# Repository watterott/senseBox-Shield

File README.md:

# senseBox-Shield
The senseBox-Shield is a plug-on module for Arduino to connect different sensor modules.

* JST connectors for different sensors
* microSD socket (SPI) support SD and SDHC cards
* RV-8523 RTC (I2C Real-Time-Clock) with backup battery
* Open-Source
* **[Documentation on learn.watterott.com](https://learn.watterott.com)**

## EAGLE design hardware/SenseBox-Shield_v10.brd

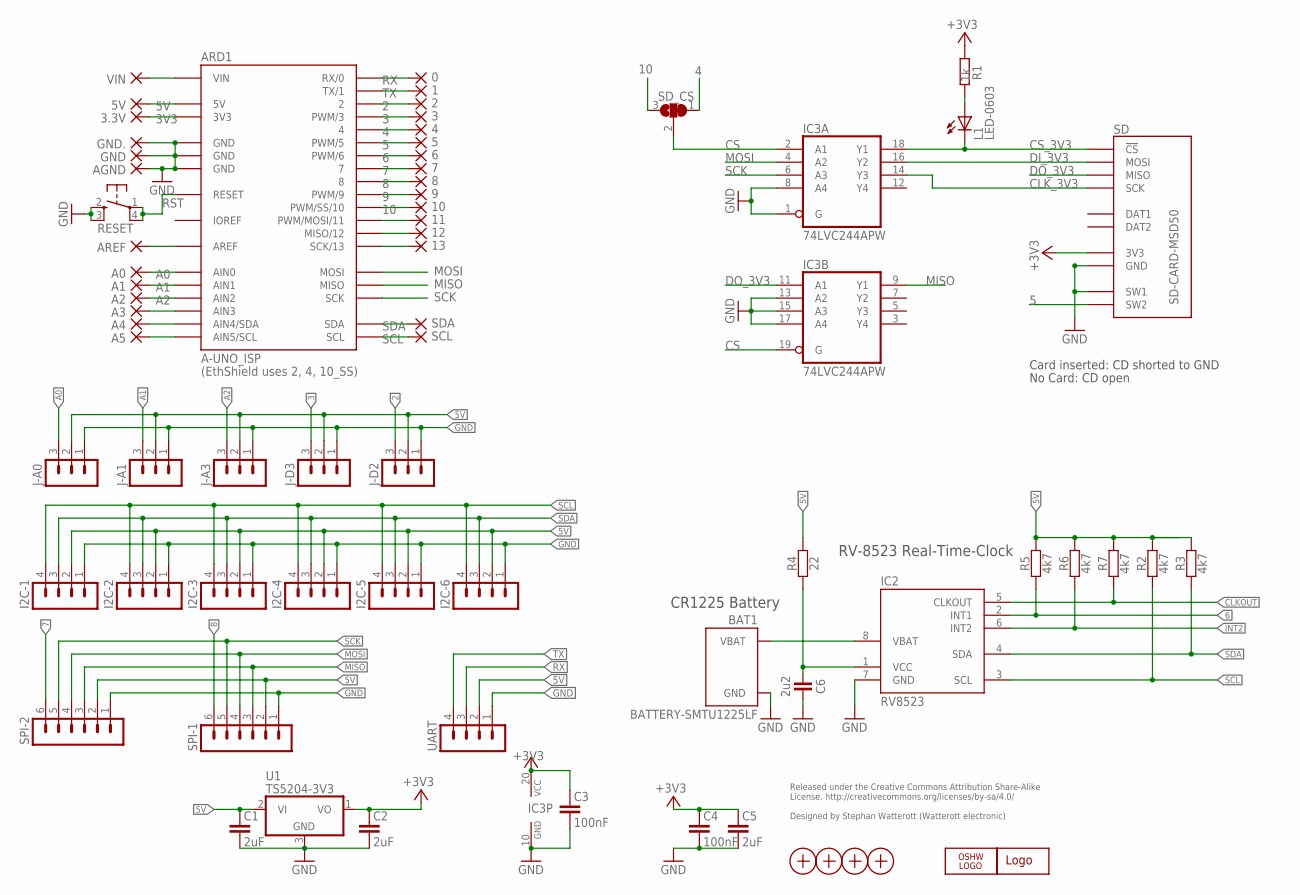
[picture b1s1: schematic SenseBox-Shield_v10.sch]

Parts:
0, 1, 2, 3, 3.3V, 4, 5, 5V, 6, 7, 8, 9, 10, 11, 12, 13: 1,6/0,8
A0, A1, A2, A3, A4, A5: 1,6/0,8
AGND: 1,6/0,8
ARD1: A-UNO_ISP; A-UNO-ISP
AREF: 1,6/0,8
BAT1: BATTERY-SMTU1225LF; BAT-SMTU1225LF
C1, C2: 2uF; C0805
C3, C4: 100nF; C0603
C5: 2uF; C0603
C6: 2u2; R0603
GND, GND.: 1,6/0,8
I2C-1, I2C-2, I2C-3, I2C-4, I2C-5, I2C-6: JST_PH_4B4B-PH-SM4-TB; JST_B4B-PH-SM4-TB
IC2: RV8523; RTC-C3
IC3: 74LVC244APW; TSSOP20
J-A0, J-A1, J-A3: JST_PH_3B3B-PH-SM4-TB; JST_B3B-PH-SM4-TB
J-D2, J-D3: JST_PH_3B3B-PH-SM4-TB; JST_B3B-PH-SM4-TB
L1: LED-0603; LED_0603
LOGO2: WE-LOGOPLACE; WE-LOGO
LOGO3: OSHW_LOGO_6MILX0100-NT; OSHW_6X100_NOTEXT
R1: 1k; R0603
R2, R3, R5, R6, R7: 4k7; R0603
R4: 22; R0603
RESET: SW4S; SW_SMD4
SCL: 1,6/0,8
SD: SD-CARD-MSD50; SD_5031821853
SDA: 1,6/0,8
SD_CS: SJ2W; SJ_2
SPI-1, SPI-2: JST_PH_6B6B-PH-SM4-TB; JST_B6B-PH-SM4-TB
U1: TS5204-3V3; SOT23
UART: JST_PH_4B4B-PH-SM4-TB; JST_B4B-PH-SM4-TB
VIN: 1,6/0,8
X1, X2, X3, X4: PASSER

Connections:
2: 2.1, ARD1.2, J-D2.3
3: 3.1, ARD1.3 (PWM/3), J-D3.3
3V3: 3.3V.1, ARD1.3V3
4: 4.1, ARD1.4, SD_CS.1
5: 5.1, ARD1.5 (PWM/5), SD.SW2
5V: 5V.1, ARD1.5V, C1.1, I2C-1.2, I2C-2.2, I2C-3.2, I2C-4.2, I2C-5.2, I2C-6.2, J-A0.2, J-A1.2, J-A3.2, J-D2.2, J-D3.2, R2.2, R3.2, R4.2, R5.2, R6.2, R7.2, SPI-1.2, SPI-2.2, U1.2 (VI), UART.2
6: 6.1, ARD1.6 (PWM/6), IC2.2 (INT1), R5.1
7: 7.1, ARD1.7, SPI-2.6
8: 8.1, ARD1.8, SPI-1.6
9: 9.1, ARD1.9 (PWM/9)
10: 10.1, ARD1.10 (PWM/SS/10), SD_CS.3
11: 11.1, ARD1.11 (PWM/MOSI/11)
12: 12.1, ARD1.12 (MISO/12)
13: 13.1, ARD1.13 (SCK/13)
+3V3: C2.1, C3.1, C4.1, C5.1, IC3.20 (VCC), R1.1, SD.VCC (3V3), U1.1 (VO)
A0: A0.1, ARD1.A0 (AIN0), J-A0.3
A1: A1.1, ARD1.A1 (AIN1), J-A1.3
A2: A2.1, ARD1.A2 (AIN2), J-A3.3
AIN3: A3.1, ARD1.A3 (AIN3)
AIN4: A4.1, ARD1.A4 (AIN4/SDA)
AIN5: A5.1, ARD1.A5 (AIN5/SCL)
AREF: ARD1.AREF, AREF.1
CLKOUT: IC2.5 (CLKOUT), R7.1
CLK_3V3: IC3.14 (Y3), SD.SCK
CS: IC3.2 (A1), IC3.19 (G), SD_CS.2
CS_3V3: IC3.18 (Y1), L1.C, SD.CS (!CS)
DI_3V3: IC3.16 (Y2), SD.MOSI
DO_3V3: IC3.11 (A1), SD.MISO
GND: AGND.1, ARD1.GND@1 (GND), ARD1.GND@2 (GND), ARD1.GND@3 (GND), BAT1.- (GND), C1.2, C2.2, C3.2, C4.2, C5.2, C6.2, GND.1, GND..1, I2C-1.1, I2C-2.1, I2C-3.1, I2C-4.1, I2C-5.1, I2C-6.1, IC2.7 (GND), IC3.1 (G), IC3.8 (A4), IC3.10 (GND), IC3.13 (A2), IC3.15 (A3), IC3.17 (A4), J-A0.1, J-A1.1, J-A3.1, J-D2.1, J-D3.1, RESET.2 (S), RESET.3 (S1), SD.GND, SD.SW1, SPI-1.1, SPI-2.1, U1.3 (GND), UART.1
INT2: IC2.6 (INT2), R6.1
IOREF: ARD1.IOREF
MISO: ARD1.MISO, IC3.9 (Y1), SPI-1.3, SPI-2.3
MOSI: ARD1.MOSI, IC3.4 (A2), SPI-1.4, SPI-2.4
unnamed: L1.A, R1.2
RST: ARD1.RST (RESET), RESET.1, RESET.4 (P1)
RV_VCC: C6.1, IC2.1 (VCC), R4.1
RX: 0.1, ARD1.0 (RX/0), UART.3
SCK: ARD1.SCK, IC3.6 (A3), SPI-1.5, SPI-2.5
SCL: ARD1.SCL, I2C-1.4, I2C-2.4, I2C-3.4, I2C-4.4, I2C-5.4, I2C-6.4, IC2.3 (SCL), R2.1, SCL.1
SDA: ARD1.SDA, I2C-1.3, I2C-2.3, I2C-3.3, I2C-4.3, I2C-5.3, I2C-6.3, IC2.4 (SDA), R3.1, SDA.1
TX: 1.1, ARD1.1 (TX/1), UART.4
VBAT: BAT1.+ (VBAT), IC2.8 (VBAT)
VIN: ARD1.VIN, VIN.1

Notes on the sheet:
Released under the Creative Commons Attribution Share-Alike License. http://creativecommons.org/licenses/by-sa/4.0/ Designed by Stephan Watterott (Watterott electronic)
(EthShield uses 2, 4, 10_SS)
Card inserted: CD shorted to GND
No Card: CD open
RV-8523 Real-Time-Clock
CR1225 Battery

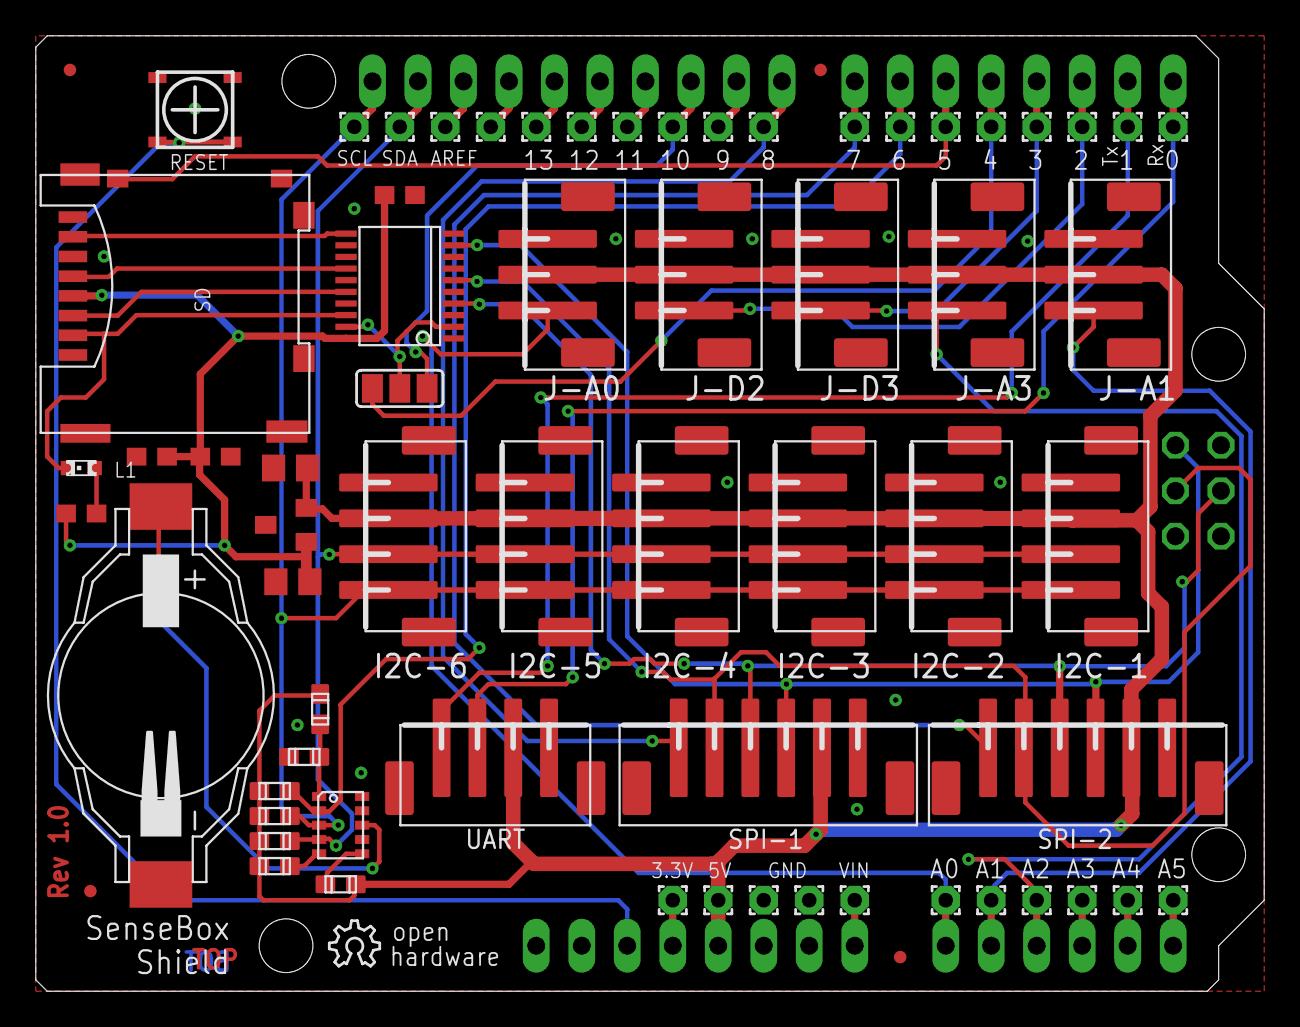
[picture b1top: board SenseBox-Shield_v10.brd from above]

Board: 2 copper layers, 68.6 x 53.3 mm, 71 parts (1 on the bottom side), 42 nets.

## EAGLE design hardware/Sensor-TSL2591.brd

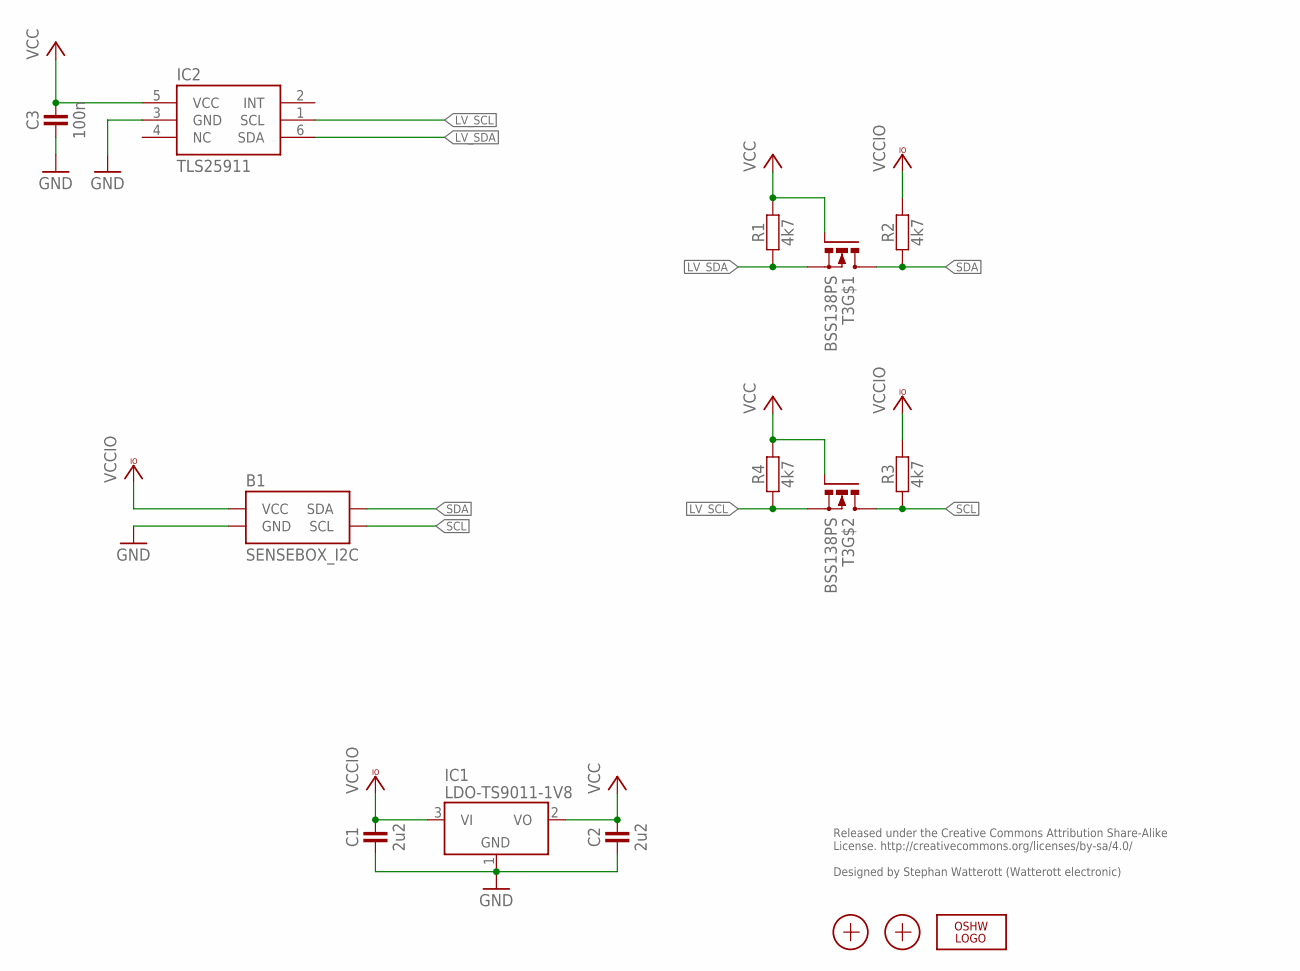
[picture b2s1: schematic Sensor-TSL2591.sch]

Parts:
B1: SENSEBOX_I2C; BREAKOUT_SENSEBOX_I2C
C1, C2: 2u2; R0402
C3: 100n; R0402
IC1: LDO-TS9011-1V8; SOT23
IC2: TLS25911; WFDFN6
LOGO2: OSHW_LOGOX0070; OSHW_6X70
R1, R2, R3, R4: 4k7; R0402
T3: BSS138PS; SOT363
X1, X2: PASSER-07; PASSER_07MM

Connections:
GND: B1.GND, C1.1, C2.1, C3.1, IC1.1 (GND), IC2.3 (GND)
LV_SCL: IC2.1 (SCL), R4.1, T3.4 (S)
LV_SDA: IC2.6 (SDA), R1.1, T3.1 (S)
SCL: B1.SCL, R3.1, T3.3 (D)
SDA: B1.SDA, R2.1, T3.6 (D)
VCC: C2.2, C3.2, IC1.2 (VO), IC2.5 (VCC), R1.2, R4.2, T3.2 (G), T3.5 (G)
VCCIO: B1.VCC, C1.2, IC1.3 (VI), R2.2, R3.2

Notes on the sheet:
Released under the Creative Commons Attribution Share-Alike License. http://creativecommons.org/licenses/by-sa/4.0/ Designed by Stephan Watterott (Watterott electronic)

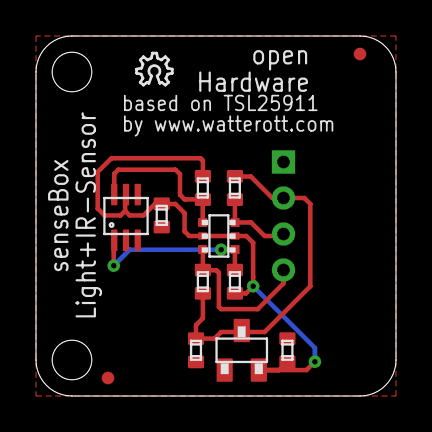
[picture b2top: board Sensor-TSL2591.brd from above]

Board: 2 copper layers, 20.0 x 20.0 mm, 14 parts (0 on the bottom side), 7 nets.

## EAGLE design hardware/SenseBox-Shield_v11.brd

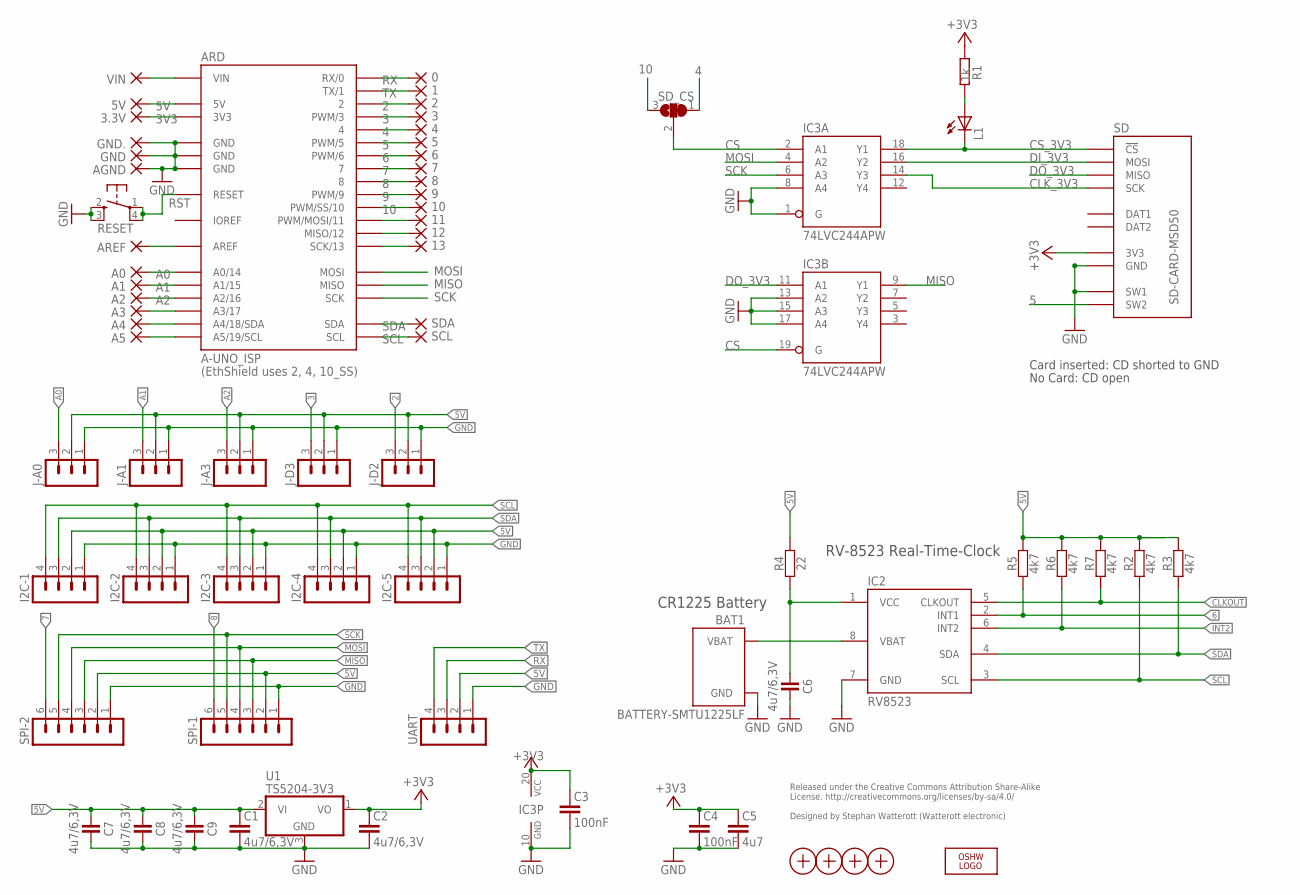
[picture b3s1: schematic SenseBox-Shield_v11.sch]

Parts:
0, 1, 2, 3, 3.3V, 4, 5, 5V, 6, 7, 8, 9, 10, 11, 12, 13: 1,6/0,8
A0, A1, A2, A3, A4, A5: 1,6/0,8
AGND: 1,6/0,8
ARD: A-UNO_ISP; A-UNO-ISP
AREF: 1,6/0,8
BAT1: BATTERY-SMTU1225LF; BAT-SMTU1225LF
C1, C2: 4u7/6,3V; C0402K
C3, C4: 100nF; C0402K
C5: 4u7; C0402K
C6, C7, C8, C9: 4u7/6,3V; C0402
GND, GND.: 1,6/0,8
I2C-1, I2C-2, I2C-3, I2C-4, I2C-5: JST_PH_4B4B-PH-SM4-TB; JST_B4B-PH-SM4-TB
IC2: RV8523; RTC-C3
IC3: 74LVC244APW; TSSOP20
J-A0, J-A1, J-A3: JST_PH_3B3B-PH-SM4-TB; JST_B3B-PH-SM4-TB
J-D2, J-D3: JST_PH_3B3B-PH-SM4-TB; JST_B3B-PH-SM4-TB
L1: LED-0603; C0603
LOGO3: OSHW_LOGO_6MILX0100-NT; OSHW_6X100_NOTEXT
R1: 1k; R0402
R2, R3, R5, R6, R7: 4k7; C0402
R4: 22; C0402
RESET: SW4S; SW_SMD4
SCL: 1,6/0,8
SD: SD-CARD-MSD50; SD_5031821853
SDA: 1,6/0,8
SD_CS: SJ2W; SJ_2
SPI-1, SPI-2: JST_PH_6B6B-PH-SM4-TB; JST_B6B-PH-SM4-TB
U1: TS5204-3V3; SOT23
UART: JST_PH_4B4B-PH-SM4-TB; JST_B4B-PH-SM4-TB
VIN: 1,6/0,8
X1, X2, X3, X4: PASSER

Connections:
2: 2.1, ARD.2, J-D2.3
3: 3.1, ARD.3 (PWM/3), J-D3.3
3V3: 3.3V.1, ARD.3V3
4: 4.1, ARD.4, SD_CS.1
5: 5.1, ARD.5 (PWM/5), SD.SW2
5V: 5V.1, ARD.5V, C1.1, C7.1, C8.1, C9.1, I2C-1.2, I2C-2.2, I2C-3.2, I2C-4.2, I2C-5.2, J-A0.2, J-A1.2, J-A3.2, J-D2.2, J-D3.2, R2.2, R3.2, R4.2, R5.2, R6.2, R7.2, SPI-1.2, SPI-2.2, U1.2 (VI), UART.2
6: 6.1, ARD.6 (PWM/6), IC2.2 (INT1), R5.1
7: 7.1, ARD.7, SPI-2.6
8: 8.1, ARD.8, SPI-1.6
9: 9.1, ARD.9 (PWM/9)
10: 10.1, ARD.10 (PWM/SS/10), SD_CS.3
11: 11.1, ARD.11 (PWM/MOSI/11)
12: 12.1, ARD.12 (MISO/12)
13: 13.1, ARD.13 (SCK/13)
+3V3: C2.1, C3.1, C4.1, C5.1, IC3.20 (VCC), R1.1, SD.VCC (3V3), U1.1 (VO)
A0: A0.1, ARD.A0 (A0/14), J-A0.3
A1: A1.1, ARD.A1 (A1/15), J-A1.3
A2: A2.1, ARD.A2 (A2/16), J-A3.3
AIN3: A3.1, ARD.A3 (A3/17)
AIN4: A4.1, ARD.A4 (A4/18/SDA)
AIN5: A5.1, ARD.A5 (A5/19/SCL)
AREF: ARD.AREF, AREF.1
CLKOUT: IC2.5 (CLKOUT), R7.1
CLK_3V3: IC3.14 (Y3), SD.SCK
CS: IC3.2 (A1), IC3.19 (G), SD_CS.2
CS_3V3: IC3.18 (Y1), L1.C, SD.CS (!CS)
DI_3V3: IC3.16 (Y2), SD.MOSI
DO_3V3: IC3.11 (A1), SD.MISO
GND: AGND.1, ARD.GND@1 (GND), ARD.GND@2 (GND), ARD.GND@3 (GND), BAT1.- (GND), C1.2, C2.2, C3.2, C4.2, C5.2, C6.2, C7.2, C8.2, C9.2, GND.1, GND..1, I2C-1.1, I2C-2.1, I2C-3.1, I2C-4.1, I2C-5.1, IC2.7 (GND), IC3.1 (G), IC3.8 (A4), IC3.10 (GND), IC3.13 (A2), IC3.15 (A3), IC3.17 (A4), J-A0.1, J-A1.1, J-A3.1, J-D2.1, J-D3.1, RESET.2 (S), RESET.3 (S1), SD.GND, SD.SW1, SPI-1.1, SPI-2.1, U1.3 (GND), UART.1
INT2: IC2.6 (INT2), R6.1
IOREF: ARD.IOREF
MISO: ARD.MISO, IC3.9 (Y1), SPI-1.3, SPI-2.3
MOSI: ARD.MOSI, IC3.4 (A2), SPI-1.4, SPI-2.4
unnamed: L1.A, R1.2
RST: ARD.RST@1 (RESET), RESET.1, RESET.4 (P1)
RV_VCC: C6.1, IC2.1 (VCC), R4.1
RX: 0.1, ARD.0 (RX/0), UART.3
SCK: ARD.SCK, IC3.6 (A3), SPI-1.5, SPI-2.5
SCL: ARD.SCL, I2C-1.4, I2C-2.4, I2C-3.4, I2C-4.4, I2C-5.4, IC2.3 (SCL), R2.1, SCL.1
SDA: ARD.SDA, I2C-1.3, I2C-2.3, I2C-3.3, I2C-4.3, I2C-5.3, IC2.4 (SDA), R3.1, SDA.1
TX: 1.1, ARD.1 (TX/1), UART.4
VBAT: BAT1.+ (VBAT), IC2.8 (VBAT)
VIN: ARD.VIN, VIN.1

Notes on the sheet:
Released under the Creative Commons Attribution Share-Alike License. http://creativecommons.org/licenses/by-sa/4.0/ Designed by Stephan Watterott (Watterott electronic)
(EthShield uses 2, 4, 10_SS)
Card inserted: CD shorted to GND
No Card: CD open
RV-8523 Real-Time-Clock
CR1225 Battery

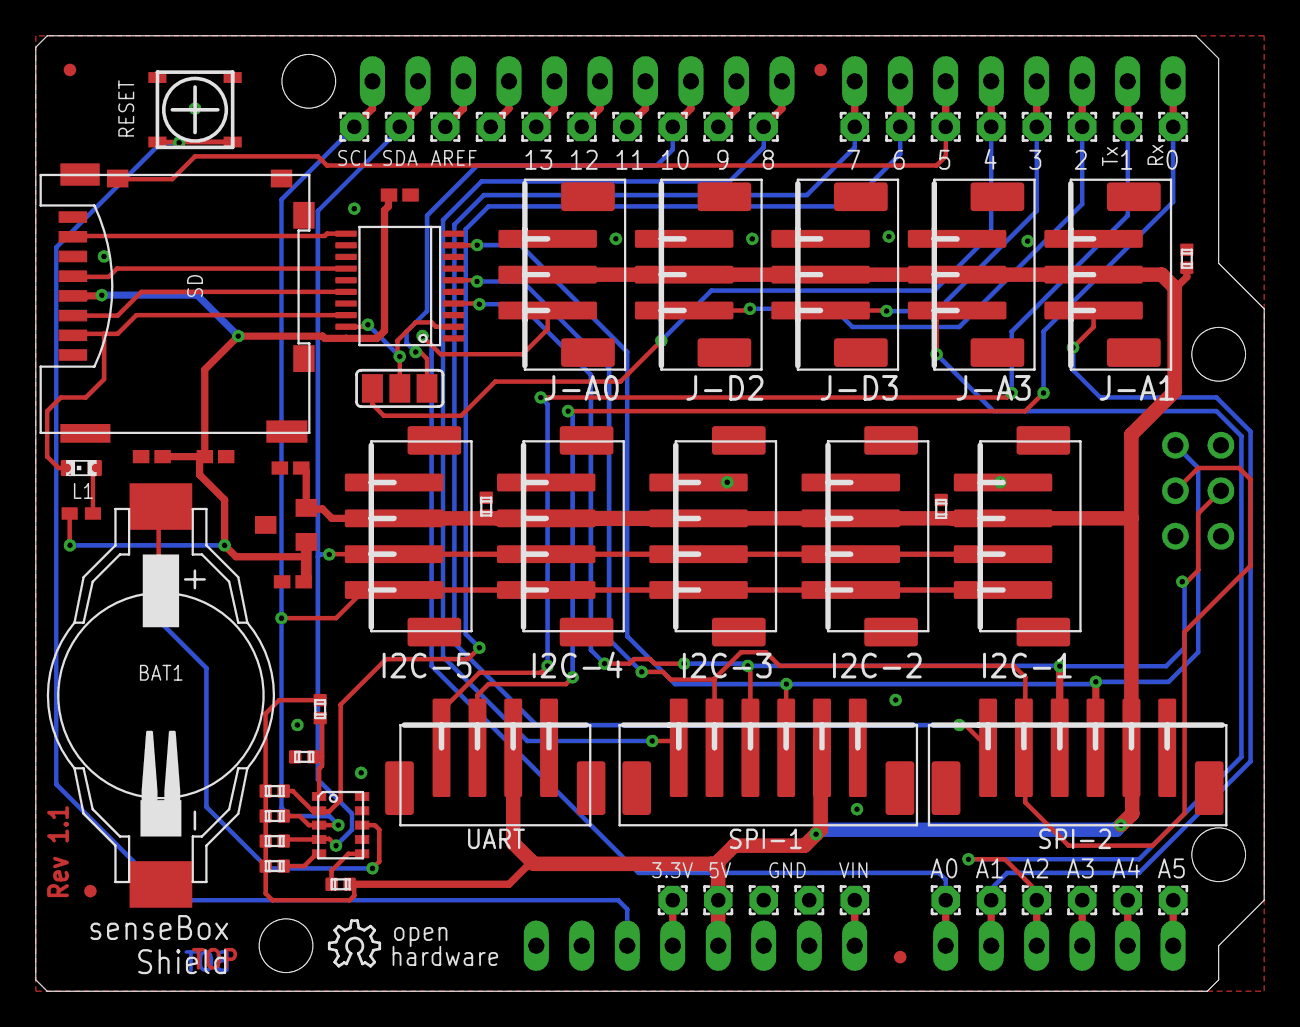
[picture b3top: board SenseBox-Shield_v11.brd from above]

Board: 2 copper layers, 68.6 x 53.3 mm, 72 parts (0 on the bottom side), 42 nets.

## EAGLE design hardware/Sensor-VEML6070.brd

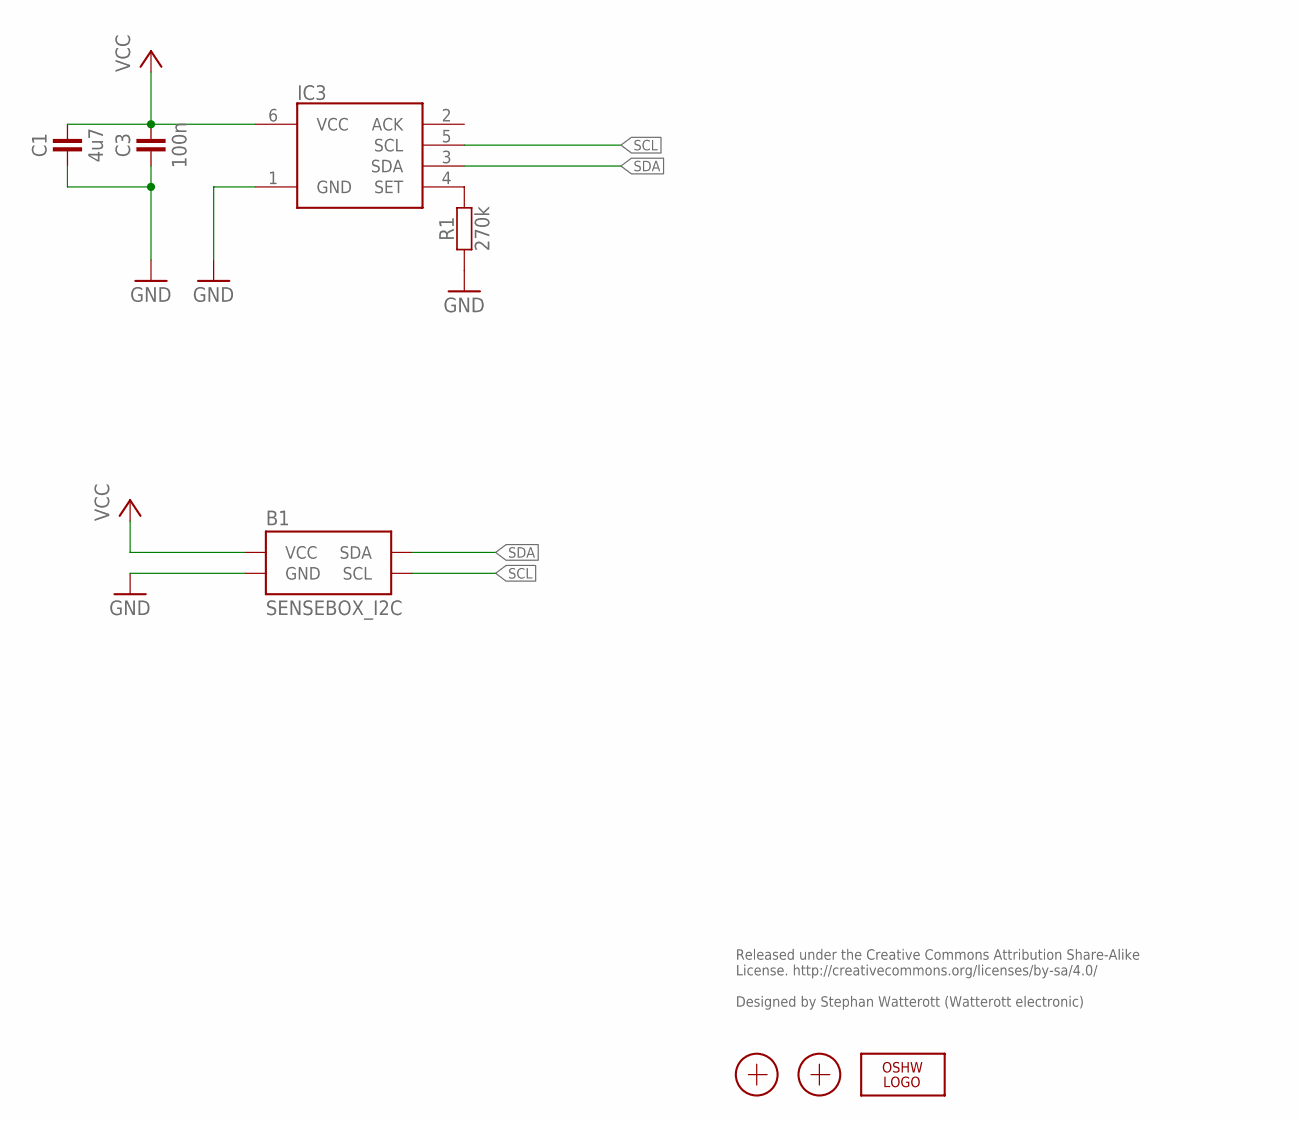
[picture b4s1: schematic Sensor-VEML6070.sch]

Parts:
B1: SENSEBOX_I2C; BREAKOUT_SENSEBOX_I2C
C1: 4u7; R0402
C3: 100n; R0402
IC3: VEML6070; OPLGA
LOGO2: OSHW_LOGOX0070; OSHW_6X70
R1: 270k; R0402
X1, X2: PASSER-07; PASSER_07MM

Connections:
GND: B1.GND, C1.1, C3.1, IC3.1 (GND), R1.1
unnamed: IC3.4 (SET), R1.2
SCL: B1.SCL, IC3.5 (SCL)
SDA: B1.SDA, IC3.3 (SDA)
VCC: B1.VCC, C1.2, C3.2, IC3.6 (VCC)

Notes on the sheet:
Released under the Creative Commons Attribution Share-Alike License. http://creativecommons.org/licenses/by-sa/4.0/ Designed by Stephan Watterott (Watterott electronic)

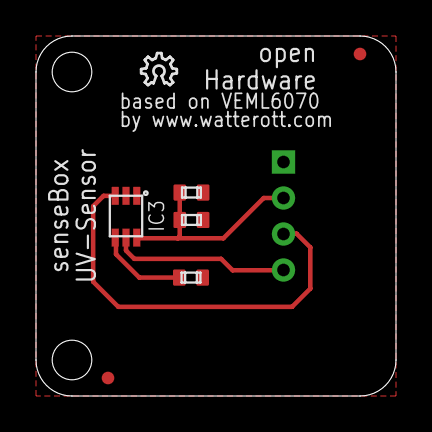
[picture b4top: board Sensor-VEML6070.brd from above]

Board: 2 copper layers, 20.0 x 20.0 mm, 8 parts (0 on the bottom side), 5 nets.

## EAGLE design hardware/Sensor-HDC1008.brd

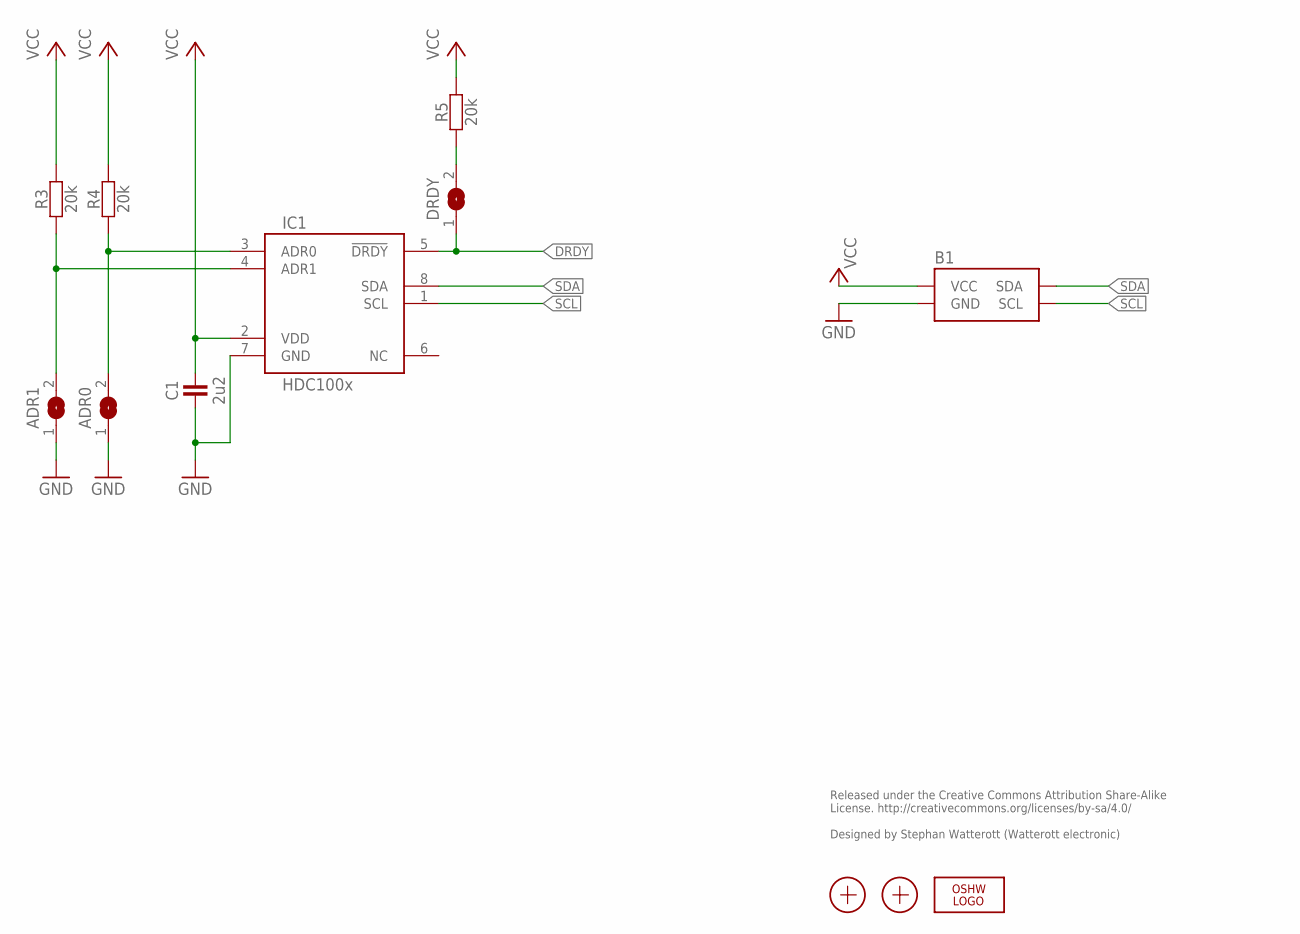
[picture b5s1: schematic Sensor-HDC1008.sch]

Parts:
ADR0, ADR1: JUMPER2-0402
B1: SENSEBOX_I2C
C1: 2u2; R0402
DRDY: JUMPER2-0402
IC1: HDC100x; WLCSP
LOGO2: OSHW_LOGOX0070; OSHW_6X70
R3, R4, R5: 20k; R0402
X1, X2: PASSER-07; PASSER_07MM

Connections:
ADR0: ADR0.2, IC1.3 (ADR0), R4.1
ADR1: ADR1.2, IC1.4 (ADR1), R3.1
DRDY: DRDY.1, IC1.5 (!DRDY)
GND: ADR0.1, ADR1.1, B1.GND, C1.1, IC1.7 (GND)
unnamed: DRDY.2, R5.1
SCL: B1.SCL, IC1.1 (SCL)
SDA: B1.SDA, IC1.8 (SDA)
VCC: B1.VCC, C1.2, IC1.2 (VDD), R3.2, R4.2, R5.2

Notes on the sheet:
Released under the Creative Commons Attribution Share-Alike License. http://creativecommons.org/licenses/by-sa/4.0/ Designed by Stephan Watterott (Watterott electronic)

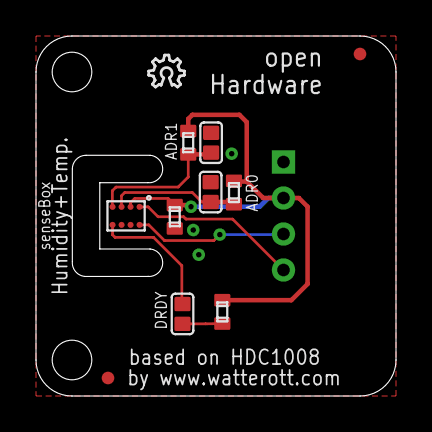
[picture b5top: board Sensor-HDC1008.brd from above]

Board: 2 copper layers, 20.0 x 20.0 mm, 12 parts (0 on the bottom side), 8 nets.
